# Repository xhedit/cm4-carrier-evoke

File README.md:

# "Evoke" CM4 Carrier Board

This is a breakout board for a CM4, maybe suitable for a DIY tablet. The original intent was a modular product, but it never happened due to component shortages. Maybe someone will find it useful.

Todo: Switch the PCIe slot to a better use of the lanes, like USB 3. TUSB7320 or UPD720202K8 is readibly available now.

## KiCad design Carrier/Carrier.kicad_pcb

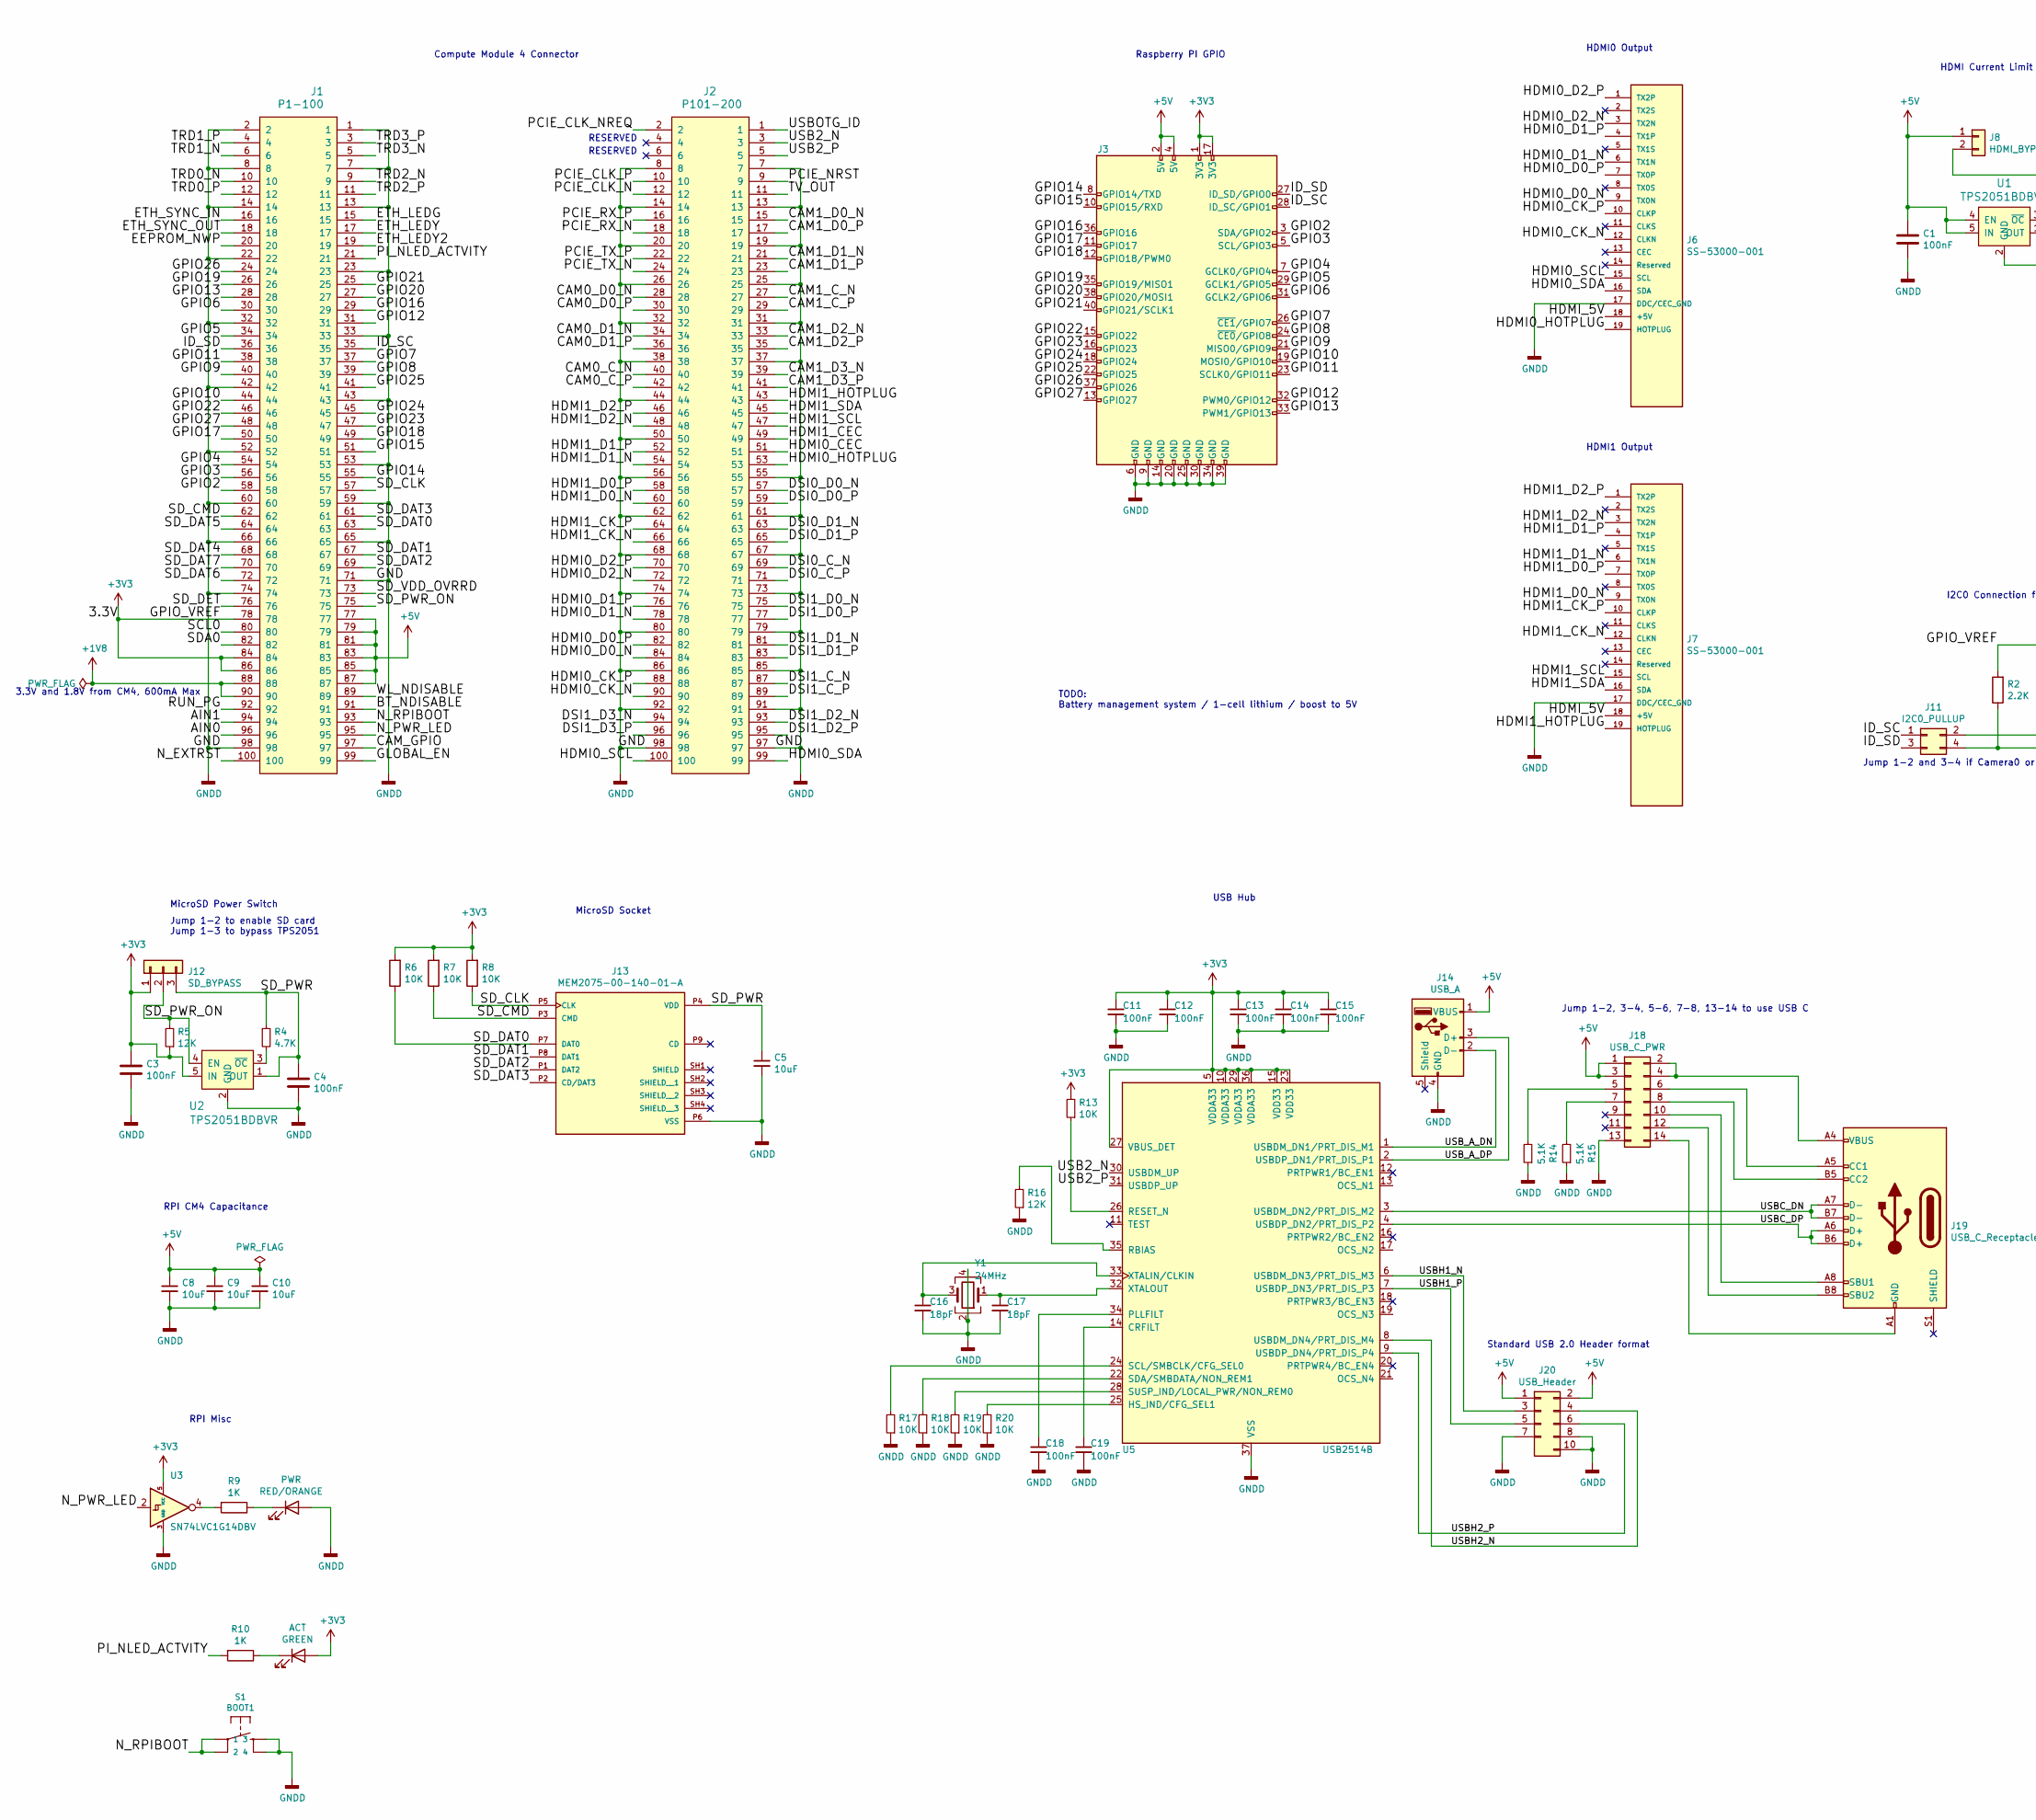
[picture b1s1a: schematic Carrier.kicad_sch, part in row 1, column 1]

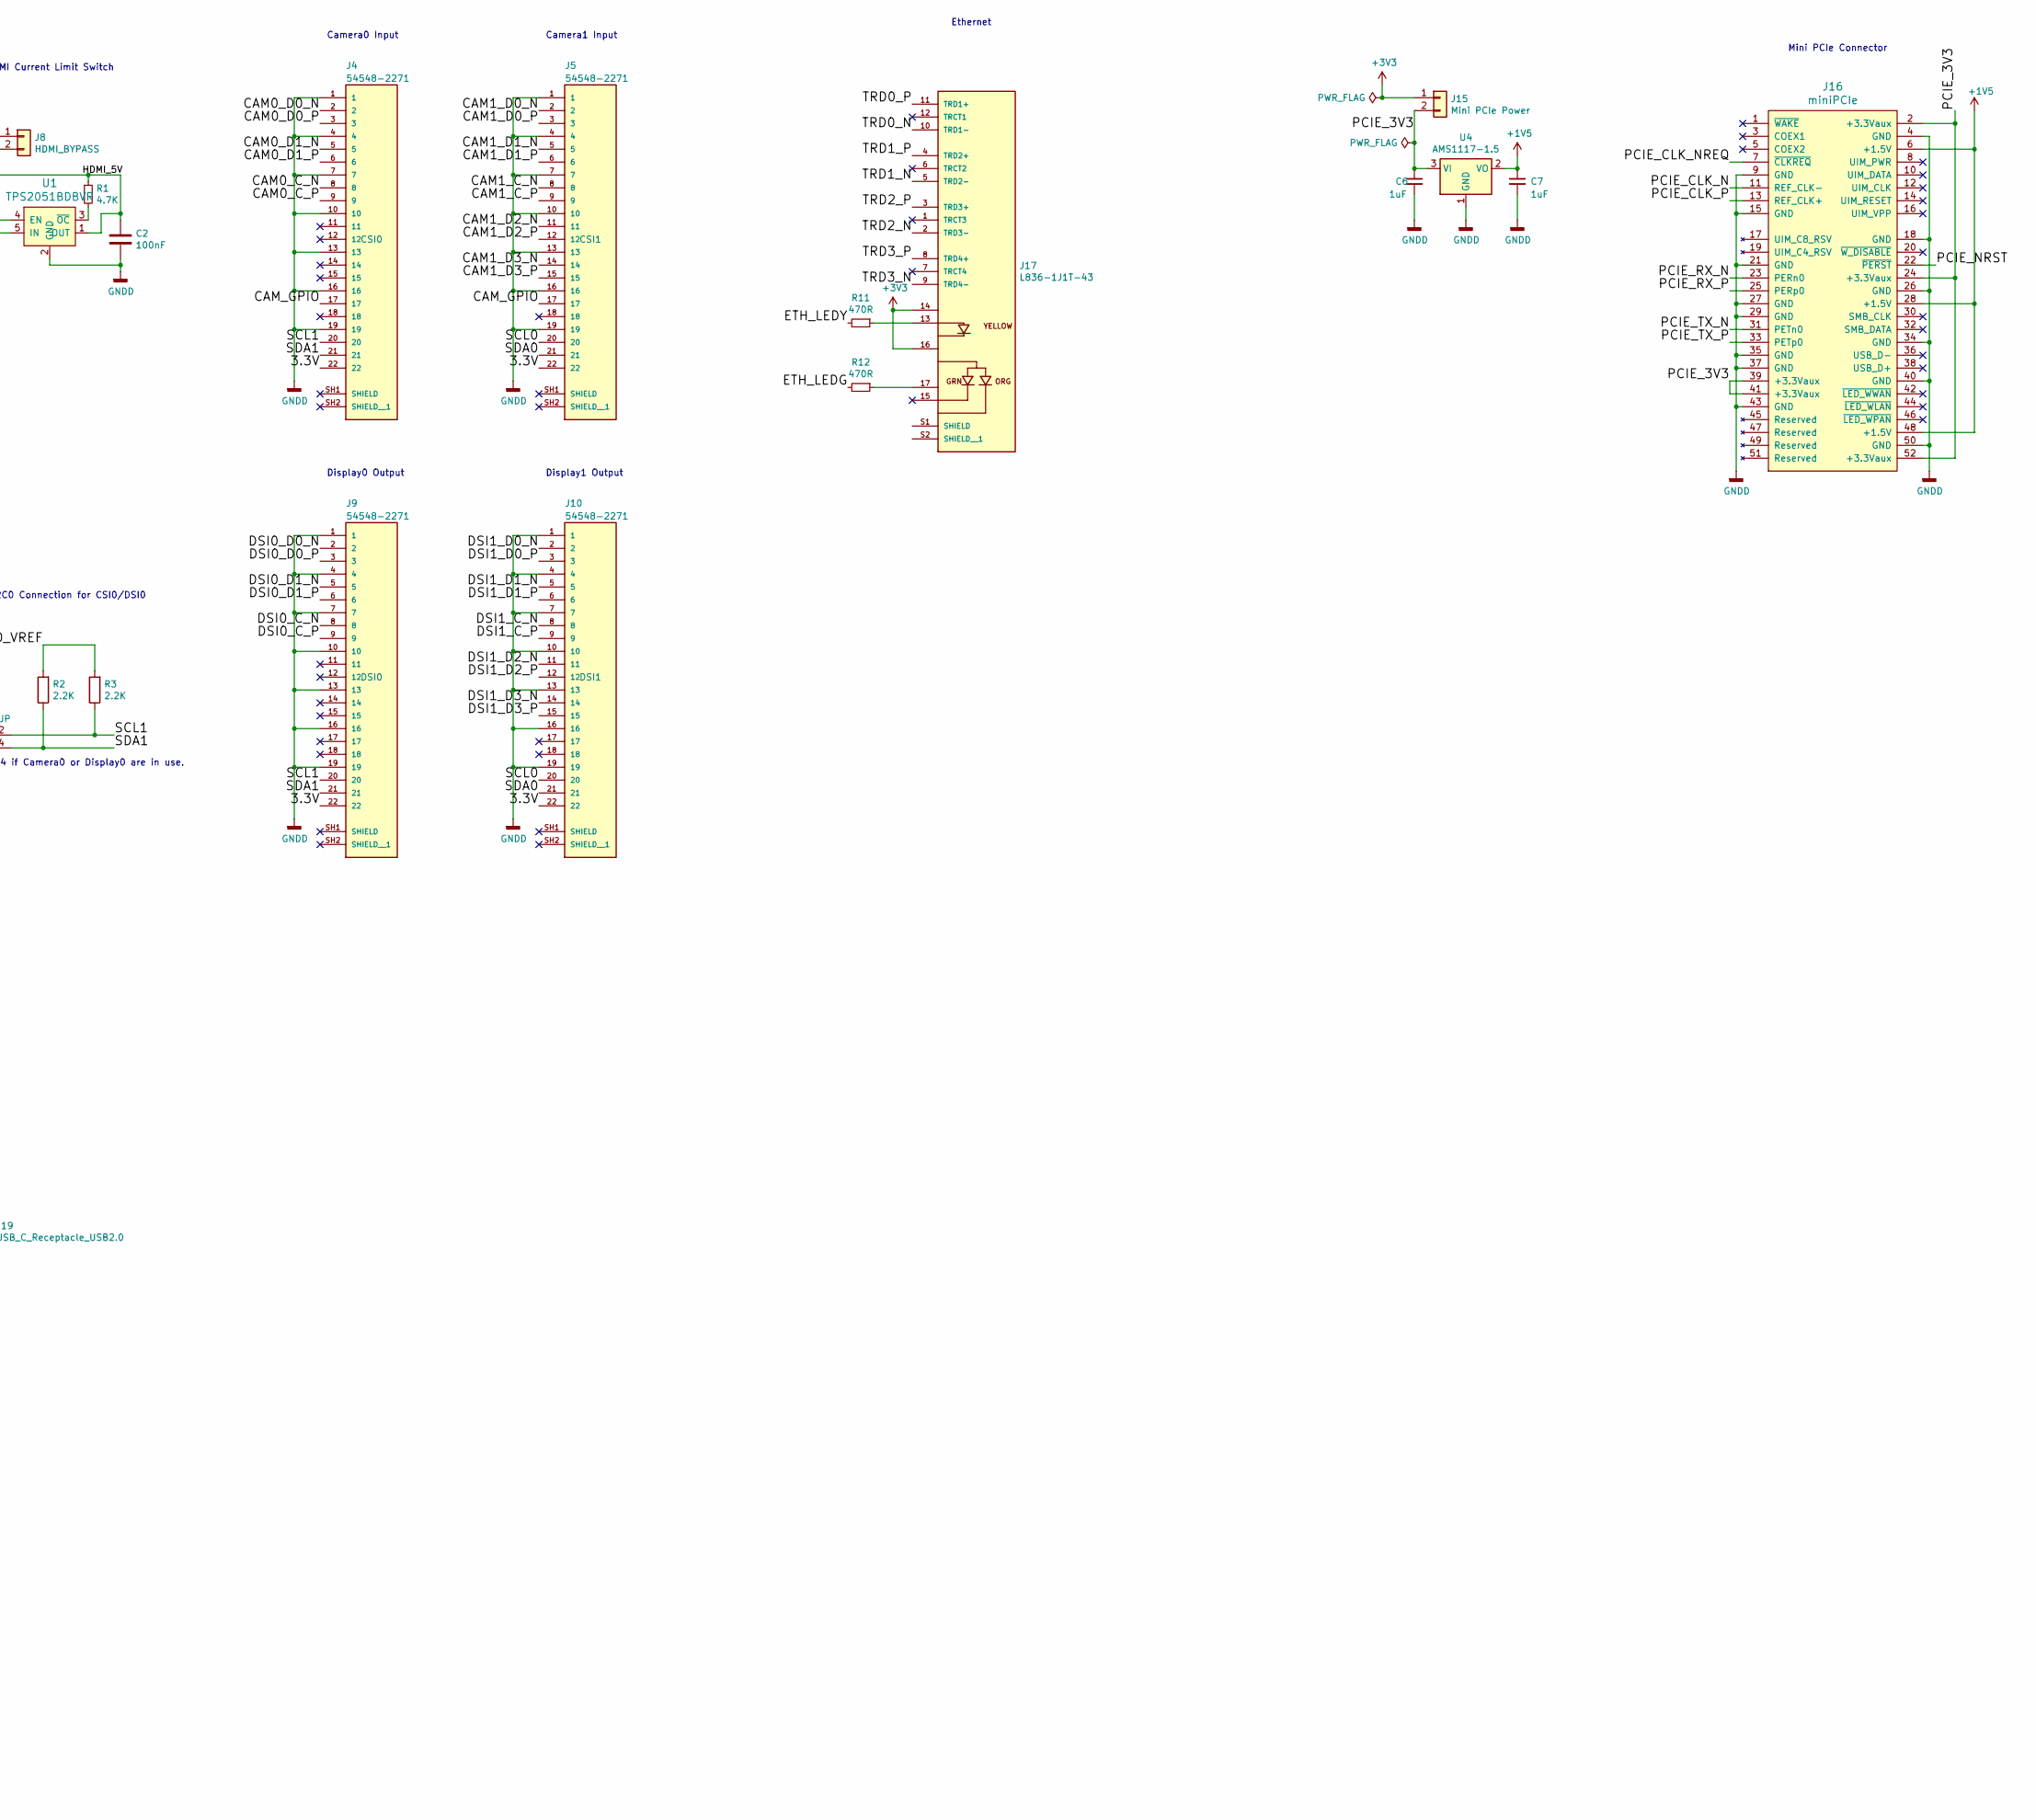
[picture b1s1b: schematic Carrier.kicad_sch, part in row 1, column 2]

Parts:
ACT: GREEN; D_0603_1608Metric
C1, C2, C3, C4, C11, C12, C13, C14, C15, C18, C19: 100nF; C_0603_1608Metric
C5, C8, C9, C10: 10uF; CP_Elec_5x4.5
C6, C7: 1uF; C_0603_1608Metric
C16, C17: 18pF; C_0603_1608Metric
J1: P1-100; HRS_DF40C-100DS-0.4V(51)
J2: P101-200; HRS_DF40C-100DS-0.4V(51)
J3: Pi GPIO; PinHeader_2x20_P1.27mm_Horizontal
J4, J5, J9, J10: 54548-2271; MOLEX_54548-2271; PARTREV N
J6, J7: SS-53000-001; STEWART_SS-53000-001; PARTREV A0
J8: HDMI_BYPASS; PinHeader_1x02_P2.54mm_Vertical
J11: I2C0_PULLUP; PinHeader_2x02_P2.54mm_Vertical
J12: SD_BYPASS; PinHeader_1x03_P2.54mm_Vertical
J13: MEM2075-00-140-01-A; GCT_MEM2075-00-140-01-A; PARTREV A
J14: USB_A; OST_USB-A1HSW6
J15: Mini PCIe Power; PinHeader_1x02_P2.54mm_Vertical
J16: miniPCIe; TE_1775862-2
J17: L836-1J1T-43; BEL_L836-1J1T-43; PARTREV B
J18: USB_C_PWR; PinHeader_2x07_P2.54mm_Vertical
J19: USB_C_Receptacle_USB2.0; USB_C_Receptacle_GCT_USB4085
J20: USB_Header; PinHeader_2x05_P2.54mm_Vertical
PWR: RED/ORANGE; D_0603_1608Metric
R1, R4: 4.7K; R_0603_1608Metric
R2, R3: 2.2K; R_0603_1608Metric
R5, R16: 12K; R_0603_1608Metric
R6, R7, R8, R13, R17, R18, R19, R20: 10K; R_0603_1608Metric
R9, R10: 1K; R_0603_1608Metric
R11, R12: 470R; R_0603_1608Metric
R14, R15: 5.1K; R_0603_1608Metric
S1: BOOT1; TACTILE_SWITCH_SMD_5.2MM
U1, U2: TPS2051BDBVR; SOT-753; MPN TPS2051BDBVR; Digi-Key_PN 296-21265-1-ND
U3: SN74LVC1G14DBV; SOT-23-5
U4: AMS1117-1.5; SOT-223-3_TabPin2
U5: USB2514B; QFN-36-1EP_6x6mm_P0.5mm_EP3.7x3.7mm
Y1: 24MHz; Crystal_SMD_2520-4Pin_2.5x2.0mm

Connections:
+1V5: C7.1, J16.6 (+1.5V), J16.28 (+1.5V), J16.48 (+1.5V), U4.2 (VO)
+1V8: J1.88, J1.90
+3V3: ACT.2 (A), C3.1, C11.1, C12.1, C13.1, C14.1, C15.1, J1.78, J1.84, J1.86, J3.1 (3V3), J3.17 (3V3), J4.22, J5.22, J9.22, J10.22, J12.1, J15.1, J17.14, J17.16, R2.2, R3.2, R5.1, R6.2, R7.2, R8.2, R13.2, U2.5 (IN), U3.5 (VCC), U5.5 (VDDA33), U5.10 (VDDA33), U5.15 (VDD33), U5.23 (VDD33), U5.27 (VBUS_DET), U5.29 (VDDA33), U5.36 (VDDA33)
+5V: C1.1, C8.1, C9.1, C10.1, J1.77, J1.79, J1.81, J1.83, J1.85, J1.87, J3.2 (5V), J3.4 (5V), J8.1, J14.1 (VBUS), J18.1, J18.3, J20.1 (5V), J20.2 (5V), U1.4 (EN), U1.5 (IN)
/AIN0: J1.96
/AIN1: J1.94
/BT_NDISABLE: J1.91
/CAM0_C_N: J2.40, J4.8
/CAM0_C_P: J2.42, J4.9
/CAM0_D0_N: J2.28, J4.2
/CAM0_D0_P: J2.30, J4.3
/CAM0_D1_N: J2.34, J4.5
/CAM0_D1_P: J2.36, J4.6
/CAM1_C_N: J2.27, J5.8
/CAM1_C_P: J2.29, J5.9
/CAM1_D0_N: J2.15, J5.2
/CAM1_D0_P: J2.17, J5.3
/CAM1_D1_N: J2.21, J5.5
/CAM1_D1_P: J2.23, J5.6
/CAM1_D2_N: J2.33, J5.11
/CAM1_D2_P: J2.35, J5.12
/CAM1_D3_N: J2.39, J5.14
/CAM1_D3_P: J2.41, J5.15
/CAM_GPIO: J1.97, J4.17, J5.17
/DSI0_C_N: J2.69, J9.8
/DSI0_C_P: J2.71, J9.9
/DSI0_D0_N: J2.57, J9.2
/DSI0_D0_P: J2.59, J9.3
/DSI0_D1_N: J2.63, J9.5
/DSI0_D1_P: J2.65, J9.6
/DSI1_C_N: J2.87, J10.8
/DSI1_C_P: J2.89, J10.9
/DSI1_D0_N: J2.75, J10.2
/DSI1_D0_P: J2.77, J10.3
/DSI1_D1_N: J2.81, J10.5
/DSI1_D1_P: J2.83, J10.6
/DSI1_D2_N: J2.93, J10.11
/DSI1_D2_P: J2.95, J10.12
/DSI1_D3_N: J2.94, J10.14
/DSI1_D3_P: J2.96, J10.15
/EEPROM_NWP: J1.20
/ETH_LEDG: J1.15, R12.2
/ETH_LEDY: J1.17, R11.2
/ETH_LEDY2: J1.19
/ETH_SYNC_IN: J1.16
/ETH_SYNC_OUT: J1.18
/GLOBAL_EN: J1.99
/GPIO2: J1.58, J3.3 (SDA/GPIO2)
/GPIO3: J1.56, J3.5 (SCL/GPIO3)
/GPIO4: J1.54, J3.7 (GCLK0/GPIO4)
/GPIO5: J1.34, J3.29 (GCLK1/GPIO5)
/GPIO6: J1.30, J3.31 (GCLK2/GPIO6)
/GPIO7: J1.37, J3.26 (~CE1/GPIO7)
/GPIO8: J1.39, J3.24 (~CE0/GPIO8)
/GPIO9: J1.40, J3.21 (MISO0/GPIO9)
/GPIO10: J1.44, J3.19 (MOSI0/GPIO10)
/GPIO11: J1.38, J3.23 (SCLK0/GPIO11)
/GPIO12: J1.31, J3.32 (PWM0/GPIO12)
/GPIO13: J1.28, J3.33 (PWM1/GPIO13)
/GPIO14: J1.55, J3.8 (GPIO14/TXD)
/GPIO15: J1.51, J3.10 (GPIO15/RXD)
/GPIO16: J1.29, J3.36 (GPIO16)
/GPIO17: J1.50, J3.11 (GPIO17)
/GPIO18: J1.49, J3.12 (GPIO18/PWM0)
/GPIO19: J1.26, J3.35 (GPIO19/MISO1)
/GPIO20: J1.27, J3.38 (GPIO20/MOSI1)
/GPIO21: J1.25, J3.40 (GPIO21/SCLK1)
/GPIO22: J1.46, J3.15 (GPIO22)
/GPIO23: J1.47, J3.16 (GPIO23)
/GPIO24: J1.45, J3.18 (GPIO24)
/GPIO25: J1.41, J3.22 (GPIO25)
/GPIO26: J1.24, J3.37 (GPIO26)
/GPIO27: J1.48, J3.13 (GPIO27)
/HDMI0_CEC: J2.51
/HDMI0_CK_N: J2.90, J6.12 (CLKN)
/HDMI0_CK_P: J2.88, J6.10 (CLKP)
/HDMI0_D0_N: J2.84, J6.9 (TX0N)
/HDMI0_D0_P: J2.82, J6.7 (TX0P)
/HDMI0_D1_N: J2.78, J6.6 (TX1N)
/HDMI0_D1_P: J2.76, J6.4 (TX1P)
/HDMI0_D2_N: J2.72, J6.3 (TX2N)
/HDMI0_D2_P: J2.70, J6.1 (TX2P)
/HDMI0_HOTPLUG: J2.53, J6.19 (HOTPLUG)
/HDMI0_SCL: J2.100, J6.15 (SCL)
/HDMI0_SDA: J2.99, J6.16 (SDA)
/HDMI1_CEC: J2.49
/HDMI1_CK_N: J2.66, J7.12 (CLKN)
/HDMI1_CK_P: J2.64, J7.10 (CLKP)
/HDMI1_D0_N: J2.60, J7.9 (TX0N)
/HDMI1_D0_P: J2.58, J7.7 (TX0P)
/HDMI1_D1_N: J2.54, J7.6 (TX1N)
/HDMI1_D1_P: J2.52, J7.4 (TX1P)
/HDMI1_D2_N: J2.48, J7.3 (TX2N)
/HDMI1_D2_P: J2.46, J7.1 (TX2P)
/HDMI1_HOTPLUG: J2.43, J7.19 (HOTPLUG)
/HDMI1_SCL: J2.47, J7.15 (SCL)
/HDMI1_SDA: J2.45, J7.16 (SDA)
/HDMI_5V: C2.1, J6.18 (+5V), J7.18 (+5V), J8.2, R1.1, U1.1 (OUT)
/ID_SC: J1.35, J3.28 (ID_SC/GPIO1), J11.1
/ID_SD: J1.36, J3.27 (ID_SD/GPIO0), J11.3
/N_EXTRST: J1.100
/N_PWR_LED: J1.95, U3.2
/N_RPIBOOT: J1.93, S1.1, S1.2
/PCIE_3V3: C6.1, J15.2, J16.2 (+3.3Vaux), J16.24 (+3.3Vaux), J16.39 (+3.3Vaux), J16.41 (+3.3Vaux), J16.52 (+3.3Vaux), U4.3 (VI)
/PCIE_CLK_N: J2.12, J16.11 (REF_CLK-)
/PCIE_CLK_NREQ: J2.2, J16.7 (~CLKREQ)
/PCIE_CLK_P: J2.10, J16.13 (REF_CLK+)
/PCIE_NRST: J2.9, J16.22 (~PERST)
/PCIE_RX_N: J2.18, J16.23 (PERn0)
/PCIE_RX_P: J2.16, J16.25 (PERp0)
/PCIE_TX_N: J2.24, J16.31 (PETn0)
/PCIE_TX_P: J2.22, J16.33 (PETp0)
/PI_NLED_ACTVITY: J1.21, R10.2
/RUN_PG: J1.92
/SCL0: J1.80, J5.20, J10.20
/SCL1: J4.20, J9.20, J11.2, R3.1
/SDA0: J1.82, J5.21, J10.21
/SDA1: J4.21, J9.21, J11.4, R2.1
/SD_CLK: J1.57, J13.P5 (CLK), R8.1
/SD_CMD: J1.62, J13.P3 (CMD), R7.1
/SD_DAT0: J1.63, J13.P7 (DAT0), R6.1
/SD_DAT1: J1.67, J13.P8 (DAT1)
/SD_DAT2: J1.69, J13.P1 (DAT2)
/SD_DAT3: J1.61, J13.P2 (CD/DAT3)
/SD_DAT4: J1.68
/SD_DAT5: J1.64
/SD_DAT6: J1.72
/SD_DAT7: J1.70
/SD_DET: J1.76
/SD_PWR: C4.1, C5.1, J12.3, J13.P4 (VDD), R4.1, U2.1 (OUT)
/SD_PWR_ON: J1.75, J12.2, R5.2, U2.4 (EN)
/SD_VDD_OVRRD: J1.73
/TRD0_N: J1.10, J17.10 (TRD1-)
/TRD0_P: J1.12, J17.11 (TRD1+)
/TRD1_N: J1.6, J17.5 (TRD2-)
/TRD1_P: J1.4, J17.4 (TRD2+)
/TRD2_N: J1.9, J17.2 (TRD3-)
/TRD2_P: J1.11, J17.3 (TRD3+)
/TRD3_N: J1.5, J17.9 (TRD4-)
/TRD3_P: J1.3, J17.8 (TRD4+)
/TV_OUT: J2.11
/USB2_N: J2.3, U5.30 (USBDM_UP)
/USB2_P: J2.5, U5.31 (USBDP_UP)
/USBC_DN: J19.A7 (D-), J19.B7 (D-), U5.3 (USBDM_DN2/PRT_DIS_M2)
/USBC_DP: J19.A6 (D+), J19.B6 (D+), U5.4 (USBDP_DN2/PRT_DIS_P2)
/USBH1_N: J20.3 (DM), U5.6 (USBDM_DN3/PRT_DIS_M3)
/USBH1_P: J20.5 (DP), U5.7 (USBDP_DN3/PRT_DIS_P3)
/USBH2_N: J20.4 (DM), U5.8 (USBDM_DN4/PRT_DIS_M4)
/USBH2_P: J20.6 (DP), U5.9 (USBDP_DN4/PRT_DIS_P4)
/USBOTG_ID: J2.1
/USB_A_DN: J14.2 (D-), U5.1 (USBDM_DN1/PRT_DIS_M1)
/USB_A_DP: J14.3 (D+), U5.2 (USBDP_DN1/PRT_DIS_P1)
/WL_NDISABLE: J1.89
GNDD: C1.2, C2.2, C3.2, C4.2, C5.2, C6.2, C7.2, C8.2, C9.2, C10.2, C11.2, C12.2, C13.2, C14.2, C15.2, C16.2, C17.2, C18.2, C19.2, J1.1, J1.2, J1.7, J1.8, J1.13, J1.14, J1.22, J1.23, J1.32, J1.33, J1.42, J1.43, J1.52, J1.53, J1.59, J1.60, J1.65, J1.66, J1.71, J1.74, J1.98, J2.7, J2.8, J2.13, J2.14, J2.19, J2.20, J2.25, J2.26, J2.31, J2.32, J2.37, J2.38, J2.44, J2.50, J2.55, J2.56, J2.61, J2.62, J2.67, J2.68, J2.73, J2.74, J2.79, J2.80, J2.85, J2.86, J2.91, J2.92, J2.97, J2.98, J3.6 (GND), J3.9 (GND), J3.14 (GND), J3.20 (GND), J3.25 (GND), J3.30 (GND), J3.34 (GND), J3.39 (GND), J4.1, J4.4, J4.7, J4.10, J4.13, J4.16, J4.19, J5.1, J5.4, J5.7, J5.10, J5.13, J5.16, J5.19, J6.17 (DDC/CEC_GND), J7.17 (DDC/CEC_GND), J9.1, J9.4, J9.7, J9.10, J9.13, J9.16, J9.19, J10.1, J10.4, J10.7, J10.10, J10.13, J10.16, J10.19, J13.P6 (VSS), J14.4 (GND), J16.4 (GND), J16.9 (GND), J16.15 (GND), J16.18 (GND), J16.21 (GND), J16.26 (GND), J16.27 (GND), J16.29 (GND), J16.34 (GND), J16.35 (GND), J16.37 (GND), J16.40 (GND), J16.43 (GND), J16.50 (GND), J18.13, J20.7 (GND), J20.8 (GND), J20.10 (NC), PWR.2 (A), R14.1, R15.1, R16.1, R17.1, R18.1, R19.1, R20.1, S1.3, S1.4, U1.2 (GND), U2.2 (GND), U3.3 (GND), U4.1 (GND), U5.37 (VSS), Y1.2, Y1.4
unnamed: ACT.1 (K), R10.1
unnamed: C16.1, U5.33 (XTALIN/CLKIN), Y1.3
unnamed: C17.1, U5.32 (XTALOUT), Y1.1
unnamed: C18.1, U5.34 (PLLFILT)
unnamed: C19.1, U5.14 (CRFILT)
unnamed: J17.13, R11.1
unnamed: J17.17, R12.1
unnamed: J18.2, J18.4, J19.A4 (VBUS), J19.A9 (VBUS), J19.B4 (VBUS), J19.B9 (VBUS)
unnamed: J18.5, R14.2
unnamed: J18.6, J19.A5 (CC1)
unnamed: J18.7, R15.2
unnamed: J18.8, J19.B5 (CC2)
unnamed: J18.10, J19.A8 (SBU1)
unnamed: J18.12, J19.B8 (SBU2)
unnamed: J18.14, J19.A1 (GND), J19.A12 (GND), J19.B1 (GND), J19.B12 (GND)
unnamed: PWR.1 (K), R9.1
unnamed: R1.2, U1.3 (~OC)
unnamed: R4.2, U2.3 (~OC)
unnamed: R9.2, U3.4
unnamed: R13.1, U5.26 (RESET_N)
unnamed: R16.2, U5.35 (RBIAS)
unnamed: R17.2, U5.24 (SCL/SMBCLK/CFG_SEL0)
unnamed: R18.2, U5.22 (SDA/SMBDATA/NON_REM1)
unnamed: R19.2, U5.28 (SUSP_IND/LOCAL_PWR/NON_REM0)
unnamed: R20.2, U5.25 (HS_IND/CFG_SEL1)

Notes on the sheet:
Compute Module 4 Connector
Mini PCIe Connector
Display0 Output
I2C0 Connection for CSI0/DSI0
HDMI Current Limit Switch
RESERVED
HDMI0 Output
Ethernet
3.3V and 1.8V from CM4, 600mA Max
Jump 1-2 and 3-4 if Camera0 or Display0 are in use.
Camera1 Input
Display1 Output
RPI CM4 Capacitance
Camera0 Input
Standard USB 2.0 Header format
MicroSD Socket
Jump 1-2, 3-4, 5-6, 7-8, 13-14 to use USB C
HDMI1 Output
MicroSD Power Switch
TODO: Battery management system / 1-cell lithium / boost to 5V
RPI Misc
USB Hub
Raspberry PI GPIO
Jump 1-2 to enable SD card Jump 1-3 to bypass TPS2051

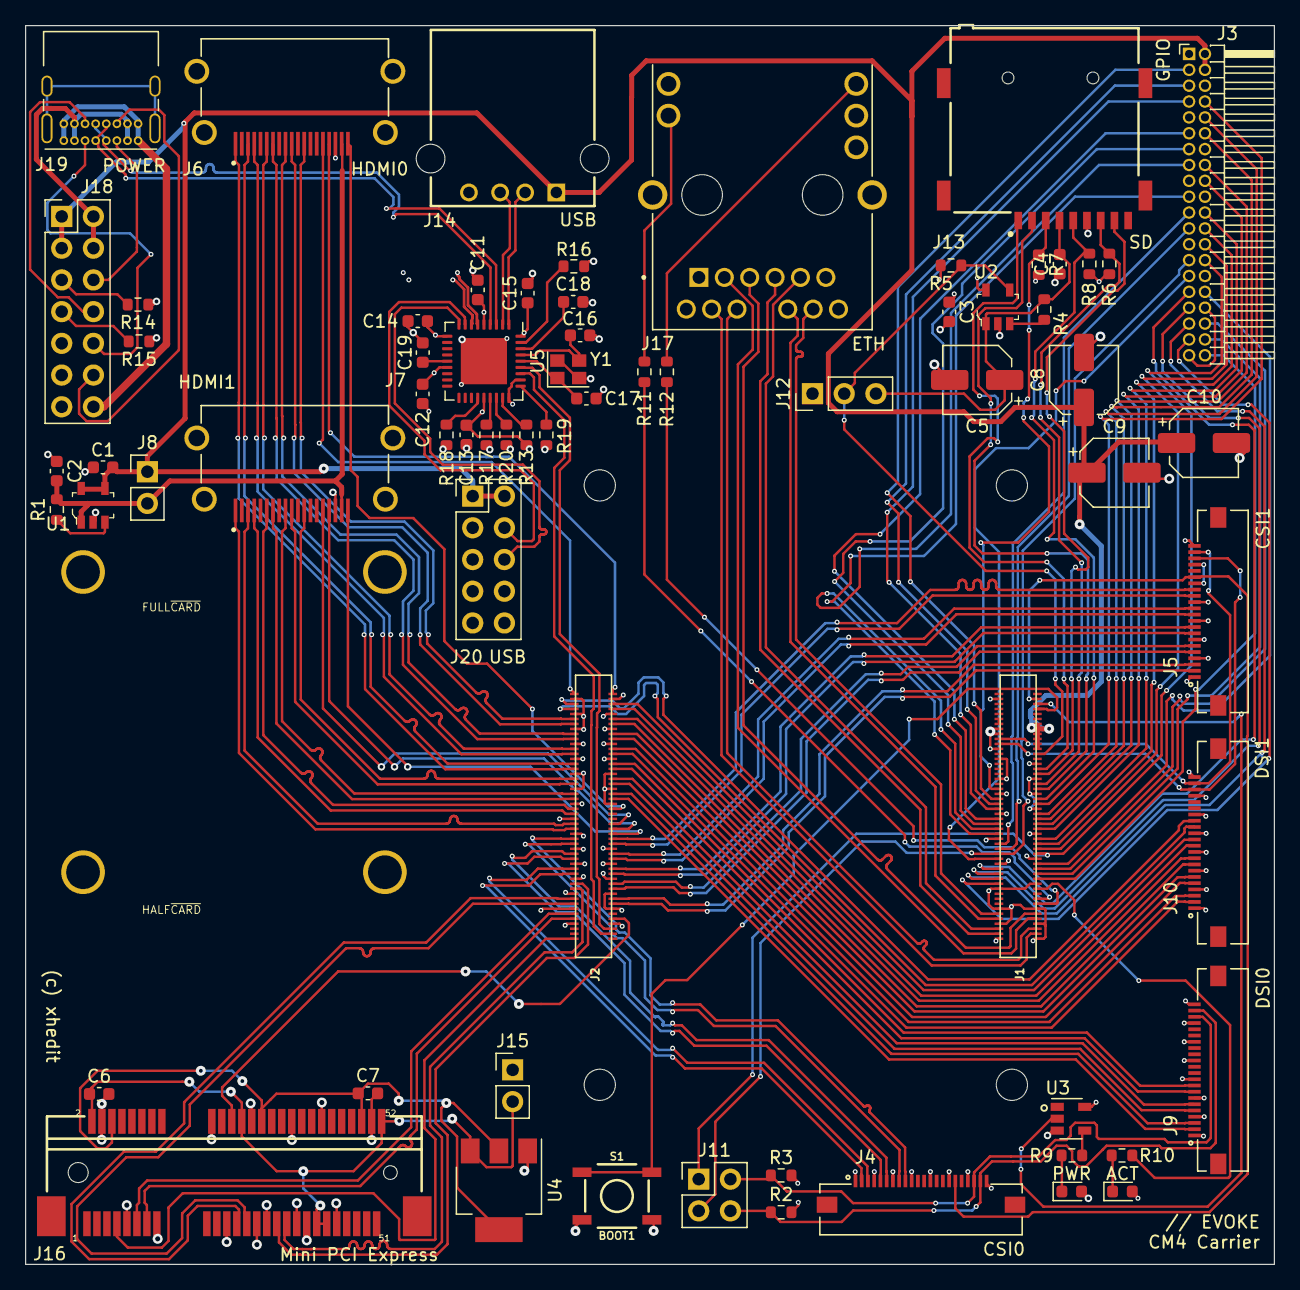
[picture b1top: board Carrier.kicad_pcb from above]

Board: 4 copper layers, 100.0 x 99.2 mm, 72 parts (0 on the bottom side), 158 nets.

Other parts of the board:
M1, M2, M3, M4: MountingHole_2.5mm

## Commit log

2024-11-29 add kicad proj files
2024-11-29 add models for 3d view
2024-11-29 add board view
